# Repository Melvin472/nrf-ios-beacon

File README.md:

📡 BeaconBlock — Mini carte d’extension NINA-B416 (LEDs + Boutons + UART)

Ce projet consiste en la création d’une petite carte électronique basée sur le module u-blox NINA-B416, comprenant :
	•	Deux LEDs avec résistances
	•	Deux boutons poussoirs
	•	Une interface UART (RX/TX) pour programmation / debug
	•	Un connecteur 1×6 (3.3V / GND / RX / TX / DTR / CTS)
	•	Les condensateurs de découplage 100 nF + 4.7 µF
	•	Une topologie propre avec plan de masse et routing optimisé

Cette carte est idéale comme module de test / dev board minimaliste pour découvrir le NINA-B416 ou développer un firmware BLE / UART / GPIO.

⸻

🧩 Contenu du projet

Le dépôt contient :

/schematic/          → Schéma KiCad
/pcb/                → Routage PCB
/gerbers/            → Fichiers de fabrication
/3d/                 → Rendu 3D (si disponible)
/README.md           → Ce fichier

⸻

🔌 Fonctionnalités principales

✔️ 1. Module NINA-B416 (nRF52840)
	•	Alimentation en 3.3V
	•	Condensateurs de découplage positionnés au plus proche :
	•	C1 → 100 nF
	•	C2 → 4.7 µF
	•	Broches utiles exposées : GPIO, UART, SWD, GND, VCC

✔️ 2. Interface UART

Connecteur 1×6 avec signalisation standard :

Pin	Fonction
1	DTR
2	RX
3	TX
4	VCC 3.3V
5	CTS
6	GND

Permet :
	•	Programmation
	•	Debug
	•	Logs série

✔️ 3. Boutons poussoirs
	•	SW1 → GPIO du NINA (IO_25)
	•	SW2 → GPIO du NINA (IO_24)
	•	Pull-down 10 kΩ inclus (R3, R4)

✔️ 4. LEDs
	•	LED1 → GPIO (LED_RED)
	•	LED2 → GPIO (LED_BLUE)
	•	Résistances de 1 kΩ (R1, R2)

⸻

🛠️ Matériel utilisé
	•	u-blox NINA-B416 (nRF52840)
	•	Condo 100 nF X7R
	•	Condo 4.7 µF
	•	Résistances 1 kΩ et 10 kΩ
	•	LED SMD 0603
	•	Boutons SMD (tact switch)
	•	Connecteur 1×6 2.54mm

⸻

⚡ Alimentation

La carte fonctionne uniquement en 3.3V.

⚠️ Attention : NE PAS alimenter le NINA en 5V !
Le module n’a pas de régulateur intégré.

⸻

📐 Routage PCB

Points clés du design :
	•	Condensateurs de découplage au plus proche des broches VCC du NINA
	•	Pistes RX/TX courtes, et côte-à-côte (pas besoin de différentiel)
	•	Plan de masse complet sur la face principale
	•	LED + résistances proches du module
	•	Boutons avec retour GND propre
	•	Via stitching recommandé autour du module (pour blindage)

⸻

🧪 Code firmware (exemple)

Un petit test pour vérifier que tout fonctionne :

void setup() {
  pinMode(LED1_PIN, OUTPUT);
  pinMode(LED2_PIN, OUTPUT);

  pinMode(SW1_PIN, INPUT);
  pinMode(SW2_PIN, INPUT);

  Serial.begin(115200);
}

void loop() {
  digitalWrite(LED1_PIN, digitalRead(SW1_PIN));
  digitalWrite(LED2_PIN, digitalRead(SW2_PIN));

  if (Serial.available()) {
    Serial.println("UART OK");
  }
}

⸻

🏭 Fabrication

Le PCB peut être fabriqué chez n’importe quel fournisseur :
	•	JLCPCB
	•	PCBWay
	•	Aisler
	•	Eurocircuits
etc.

Paramètres recommandés :
	•	Épaisseur : 1.6 mm
	•	Couleur : libre
	•	Cuivre : 1 oz
	•	Masque : standard
	•	Finition : HASL ou ENIG

⸻

📦 Assemblage

Gestion des composants :
	•	LED → attention à l’orientation
	•	Boutons → pads symétriques, easy
	•	NINA-B416 → nécessite reflow (hot air ou four), pas soudable au fer
	•	Vérifier l’exposed pad GND

⸻

🚀 Statut du projet

✔ Schéma terminé
✔ PCB routé
✔ Vérification électrique OK
⬜ Test électrique
⬜ Test firmware

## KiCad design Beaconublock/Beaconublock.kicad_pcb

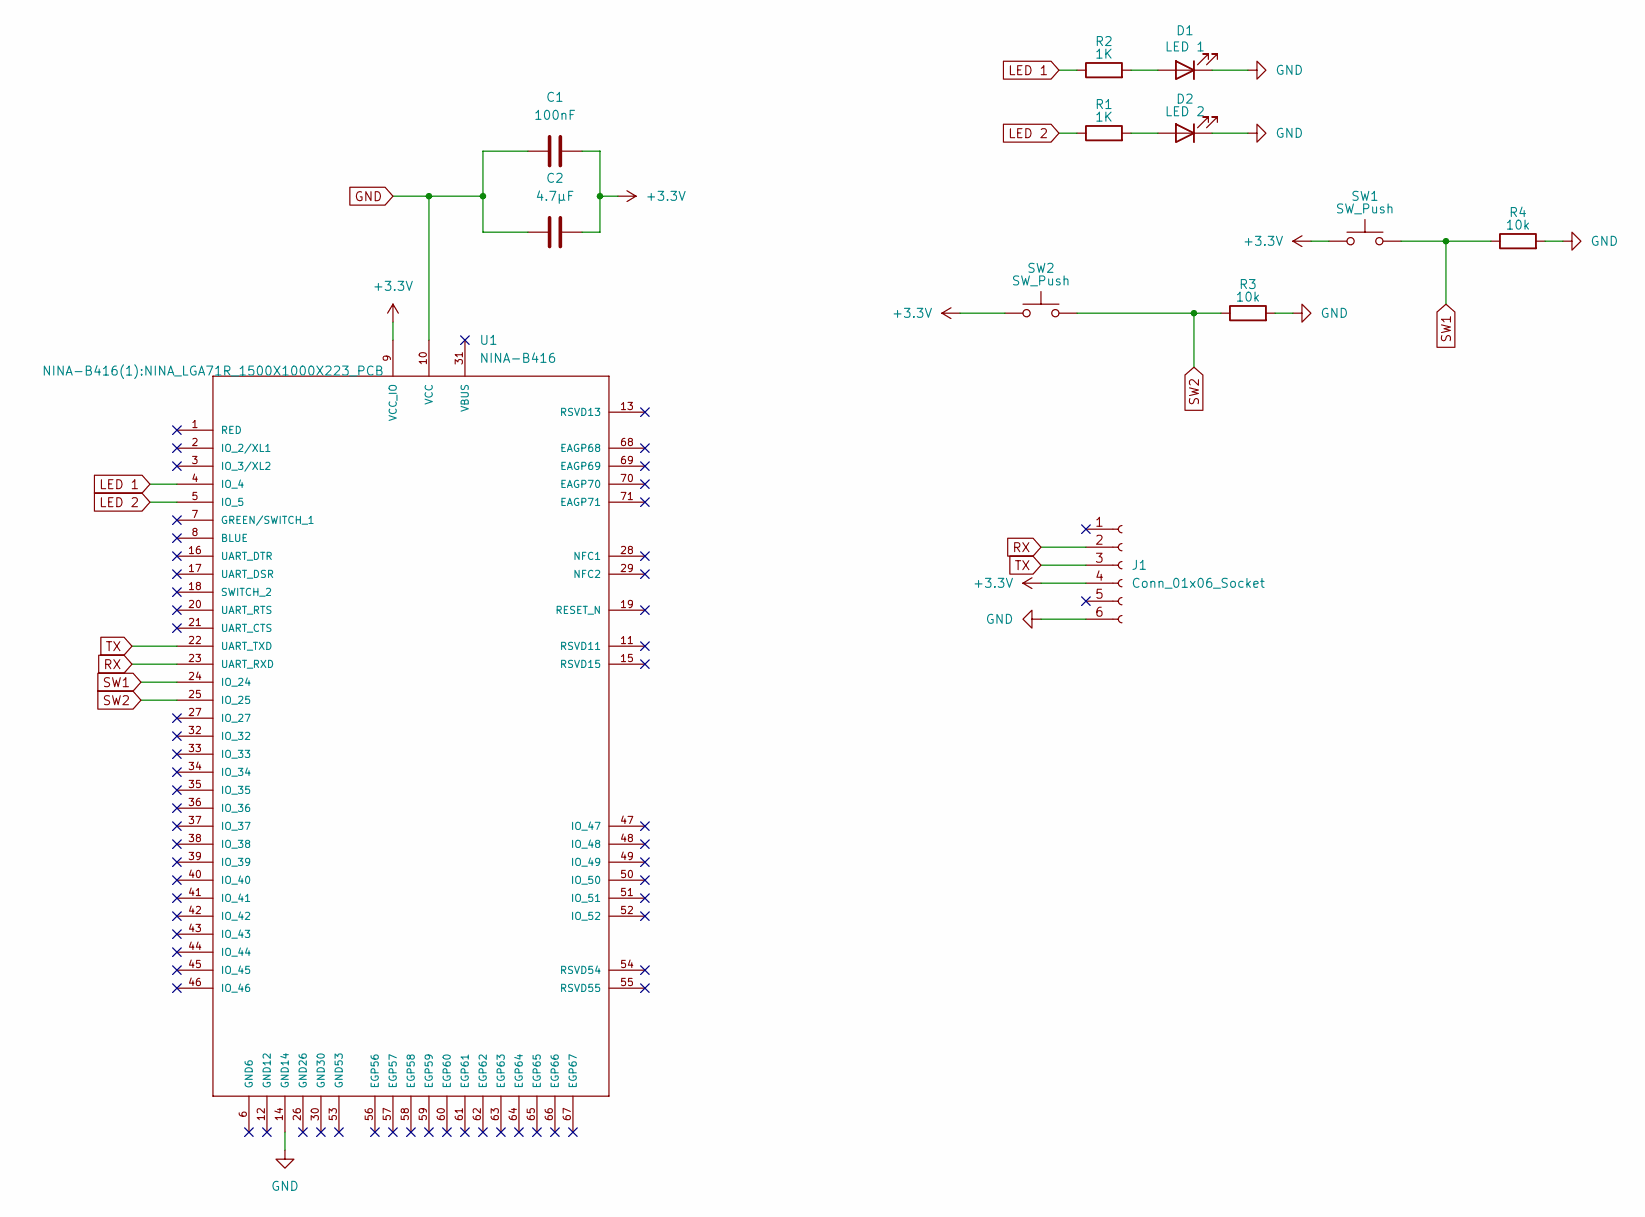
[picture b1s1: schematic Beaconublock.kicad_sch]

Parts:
C1: 100nF; C_0805_2012Metric_Pad1.18x1.45mm_HandSolder
C2: 4.7µF; C_0805_2012Metric_Pad1.18x1.45mm_HandSolder
D1: LED 1; LED_0805_2012Metric_Pad1.15x1.40mm_HandSolder
D2: LED 2; LED_0805_2012Metric_Pad1.15x1.40mm_HandSolder
J1: Conn_01x06_Socket; PinSocket_1x06_P2.54mm_Vertical
R1, R2: 1K; R_0805_2012Metric_Pad1.20x1.40mm_HandSolder
R3, R4: 10k; R_0805_2012Metric_Pad1.20x1.40mm_HandSolder
SW1, SW2: SW_Push; SW_DIP_SPSTx01_Slide_Copal_CHS-01A_W5.08mm_P1.27mm_JPin
U1: NINA-B416; NINA_LGA71R_1500X1000X223_PCB; PART_DESCRIPTION Stand-alone Bluetooth low energy module

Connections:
+3.3V: C1.1, C2.1, J1.4, SW1.1, SW2.1, U1.9 (VCC_IO)
GND: C1.2, C2.2, D1.1 (K), D2.1 (K), J1.6, R3.2, R4.2, U1.10 (VCC), U1.14 (GND14)
LED 1: R2.1, U1.4 (IO_4)
LED 2: R1.1, U1.5 (IO_5)
unnamed: D1.2 (A), R2.2
unnamed: D2.2 (A), R1.2
RX: J1.2, U1.23 (UART_RXD)
SW1: R4.1, SW1.2, U1.24 (IO_24)
SW2: R3.1, SW2.2, U1.25 (IO_25)
TX: J1.3, U1.22 (UART_TXD)

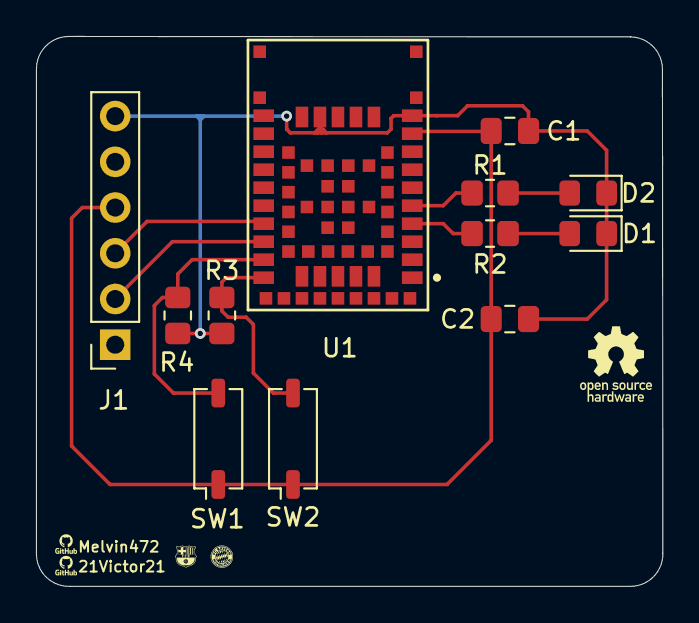
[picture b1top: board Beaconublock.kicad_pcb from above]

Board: 2 copper layers, 34.8 x 30.6 mm, 12 parts (0 on the bottom side), 10 nets.

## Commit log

2025-10-24 [skip lovable] Use tech stack vite_react_shadcn_ts_20250728_minor
2025-10-24 Add nRF52833 iOS app
2025-10-24 Fix: Handle Bluetooth scan initialization error
2025-10-24 Fix: Improve Bluetooth scanning and device discovery
2025-10-24 Fix Bluetooth scanning issues
2025-10-24 Fix Xcode console warnings
2025-10-31 feat: Display more device details
2025-11-06 Add device details and info
2025-11-06 feat: Display data without sending
2025-11-06 Fix: Improve device information display
2025-11-06 Implement writeable characteristics and battery info
    This commit addresses two main issues:
    - **Writeable Characteristics:** Implemented the ability to write data to BLE characteristics that support the 'write' property. This allows for two-way communication with BLE devices.
    - **Battery Information:** Resolved the issue where battery percentage was not being displayed. The code now correctly reads and displays the battery level for connected devices.
    Additionally, the commit includes:
    - Enhanced error handling for reading characteristics, providing more informative messages when data cannot be accessed.
    - Refined the display of device information for better clarity.
2025-11-06 Implement writable characteristics
    The AI implemented the ability to write to BLE characteristics that support it, by adding an `Input` field and `Send` button next to each writable characteristic in `src/components/DeviceConnection.t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
    Regarding the issue of not seeing iPhone battery percentage or other details:
    - The AI explained that iPhones restrict access to system information (like battery level) via BLE for security and privacy, unless the devices are paired.
    - The `readAllCharacteristics` function in `src/components/DeviceConnection.tsx` was further improved with detailed conso
2025-12-12 Ajout Kicad
